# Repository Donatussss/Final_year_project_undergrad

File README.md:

# Water and Gas monitoring for automated oxygen and hydrogen production through electrolysis

### Project Aims
- Meet oxygen demand in hospitals
- Realise an affordable device to generate oxygen

This is our final year undergrad project
## Project designations
- Elec team
  - Monitor water levels in electrolysis chambers - Mitch
  - Monitor gas pressure, flowrate and concentration - Don

- Mech team
  - Dominic & Alphonso - develop electrolysis chamber

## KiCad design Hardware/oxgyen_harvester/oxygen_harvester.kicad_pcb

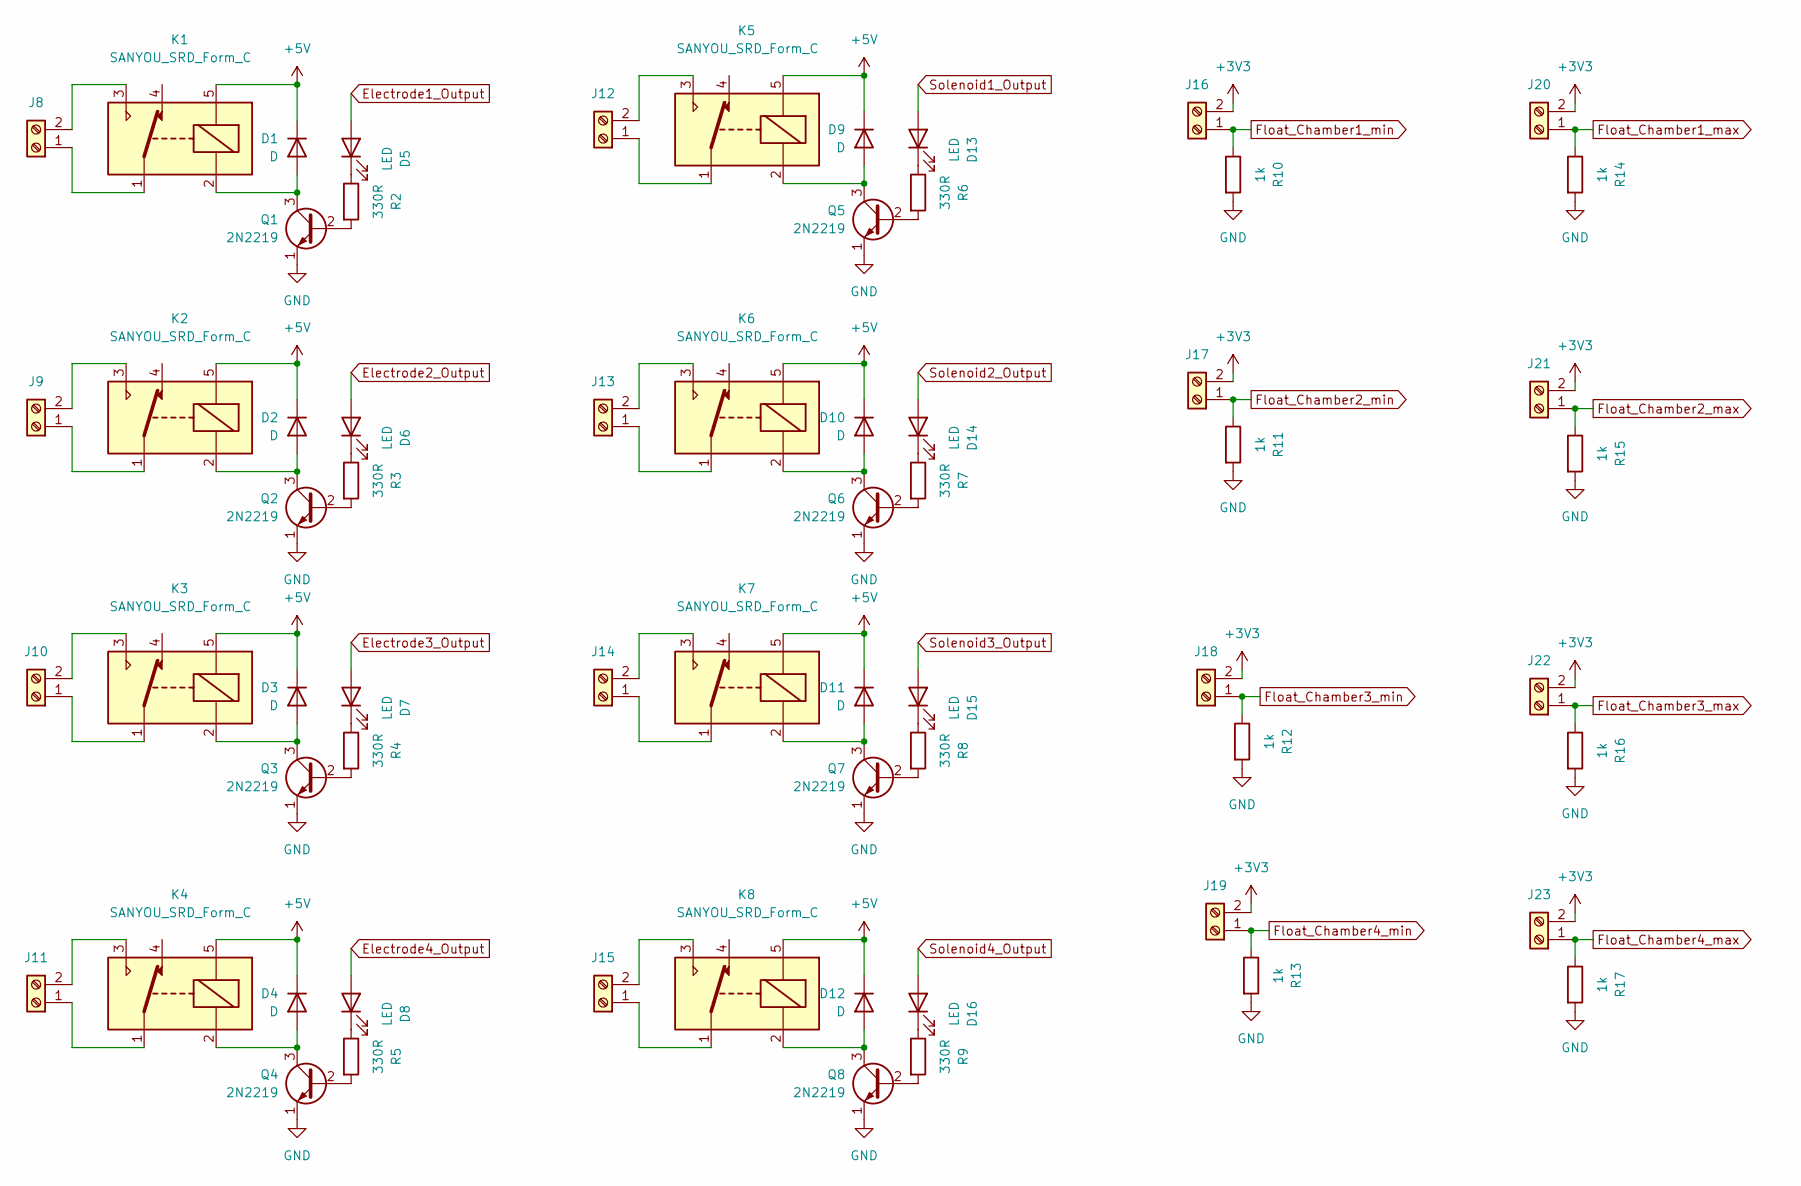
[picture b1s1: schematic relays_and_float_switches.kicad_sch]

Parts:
D1, D2, D3, D4, D9, D10, D11, D12: D; D_A-405_P10.16mm_Horizontal
D5, D6, D7, D8, D13, D14, D15, D16: LED; LED_D5.0mm_IRBlack
J8, J9, J10, J11, J12, J13, J14, J15, J16, J17, J18, J19, J20, J21, J22, J23: Screw_Terminal_01x02; TerminalBlock_bornier-2_P5.08mm
K1, K2, K3, K4, K5, K6, K7, K8: SANYOU_SRD_Form_C; Relay_SPDT_SANYOU_SRD_Series_Form_C
Q1, Q2, Q3, Q4, Q5, Q6, Q7, Q8: 2N2219; TO-92L_Inline
R2, R3, R4, R5, R6, R7, R8, R9: 330R; R_Axial_DIN0207_L6.3mm_D2.5mm_P10.16mm_Horizontal
R10, R11, R12, R13, R14, R15, R16, R17: 1k; R_Axial_DIN0207_L6.3mm_D2.5mm_P10.16mm_Horizontal

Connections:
+3V3: J16.2, J17.2, J18.2, J19.2, J20.2, J21.2, J22.2, J23.2; also elsewhere on the board
+5V: D1.1 (K), D2.1 (K), D3.1 (K), D4.1 (K), D9.1 (K), D10.1 (K), D11.1 (K), D12.1 (K), K1.5, K2.5, K3.5, K4.5, K5.5, K6.5, K7.5, K8.5; also elsewhere on the board
Electrode1_Output: D5.2 (A); also elsewhere on the board
Electrode2_Output: D6.2 (A); also elsewhere on the board
Electrode3_Output: D7.2 (A); also elsewhere on the board
Electrode4_Output: D8.2 (A); also elsewhere on the board
Float_Chamber1_max: J20.1, R14.1; also elsewhere on the board
Float_Chamber1_min: J16.1, R10.1; also elsewhere on the board
Float_Chamber2_max: J21.1, R15.1; also elsewhere on the board
Float_Chamber2_min: J17.1, R11.1; also elsewhere on the board
Float_Chamber3_max: J22.1, R16.1; also elsewhere on the board
Float_Chamber3_min: J18.1, R12.1; also elsewhere on the board
Float_Chamber4_max: J23.1, R17.1; also elsewhere on the board
Float_Chamber4_min: J19.1, R13.1; also elsewhere on the board
GND: Q1.1 (E), Q2.1 (E), Q3.1 (E), Q4.1 (E), Q5.1 (E), Q6.1 (E), Q7.1 (E), Q8.1 (E), R10.2, R11.2, R12.2, R13.2, R14.2, R15.2, R16.2, R17.2; also elsewhere on the board
unnamed: D1.2 (A), K1.2, Q1.3 (C)
unnamed: D2.2 (A), K2.2, Q2.3 (C)
unnamed: D3.2 (A), K3.2, Q3.3 (C)
unnamed: D4.2 (A), K4.2, Q4.3 (C)
unnamed: D5.1 (K), R2.1
unnamed: D6.1 (K), R3.1
unnamed: D7.1 (K), R4.1
unnamed: D8.1 (K), R5.1
unnamed: D9.2 (A), K5.2, Q5.3 (C)
unnamed: D10.2 (A), K6.2, Q6.3 (C)
unnamed: D11.2 (A), K7.2, Q7.3 (C)
unnamed: D12.2 (A), K8.2, Q8.3 (C)
unnamed: D13.1 (K), R6.1
unnamed: D14.1 (K), R7.1
unnamed: D15.1 (K), R8.1
unnamed: D16.1 (K), R9.1
unnamed: J8.1, K1.1
unnamed: J8.2, K1.3
unnamed: J9.1, K2.1
unnamed: J9.2, K2.3
unnamed: J10.1, K3.1
unnamed: J10.2, K3.3
unnamed: J11.1, K4.1
unnamed: J11.2, K4.3
unnamed: J12.1, K5.1
unnamed: J12.2, K5.3
unnamed: J13.1, K6.1
unnamed: J13.2, K6.3
unnamed: J14.1, K7.1
unnamed: J14.2, K7.3
unnamed: J15.1, K8.1
unnamed: J15.2, K8.3
unnamed: Q1.2 (B), R2.2
unnamed: Q2.2 (B), R3.2
unnamed: Q3.2 (B), R4.2
unnamed: Q4.2 (B), R5.2
unnamed: Q5.2 (B), R6.2
unnamed: Q6.2 (B), R7.2
unnamed: Q7.2 (B), R8.2
unnamed: Q8.2 (B), R9.2
Solenoid1_Output: D13.2 (A); also elsewhere on the board
Solenoid2_Output: D14.2 (A); also elsewhere on the board
Solenoid3_Output: D15.2 (A); also elsewhere on the board
Solenoid4_Output: D16.2 (A); also elsewhere on the board

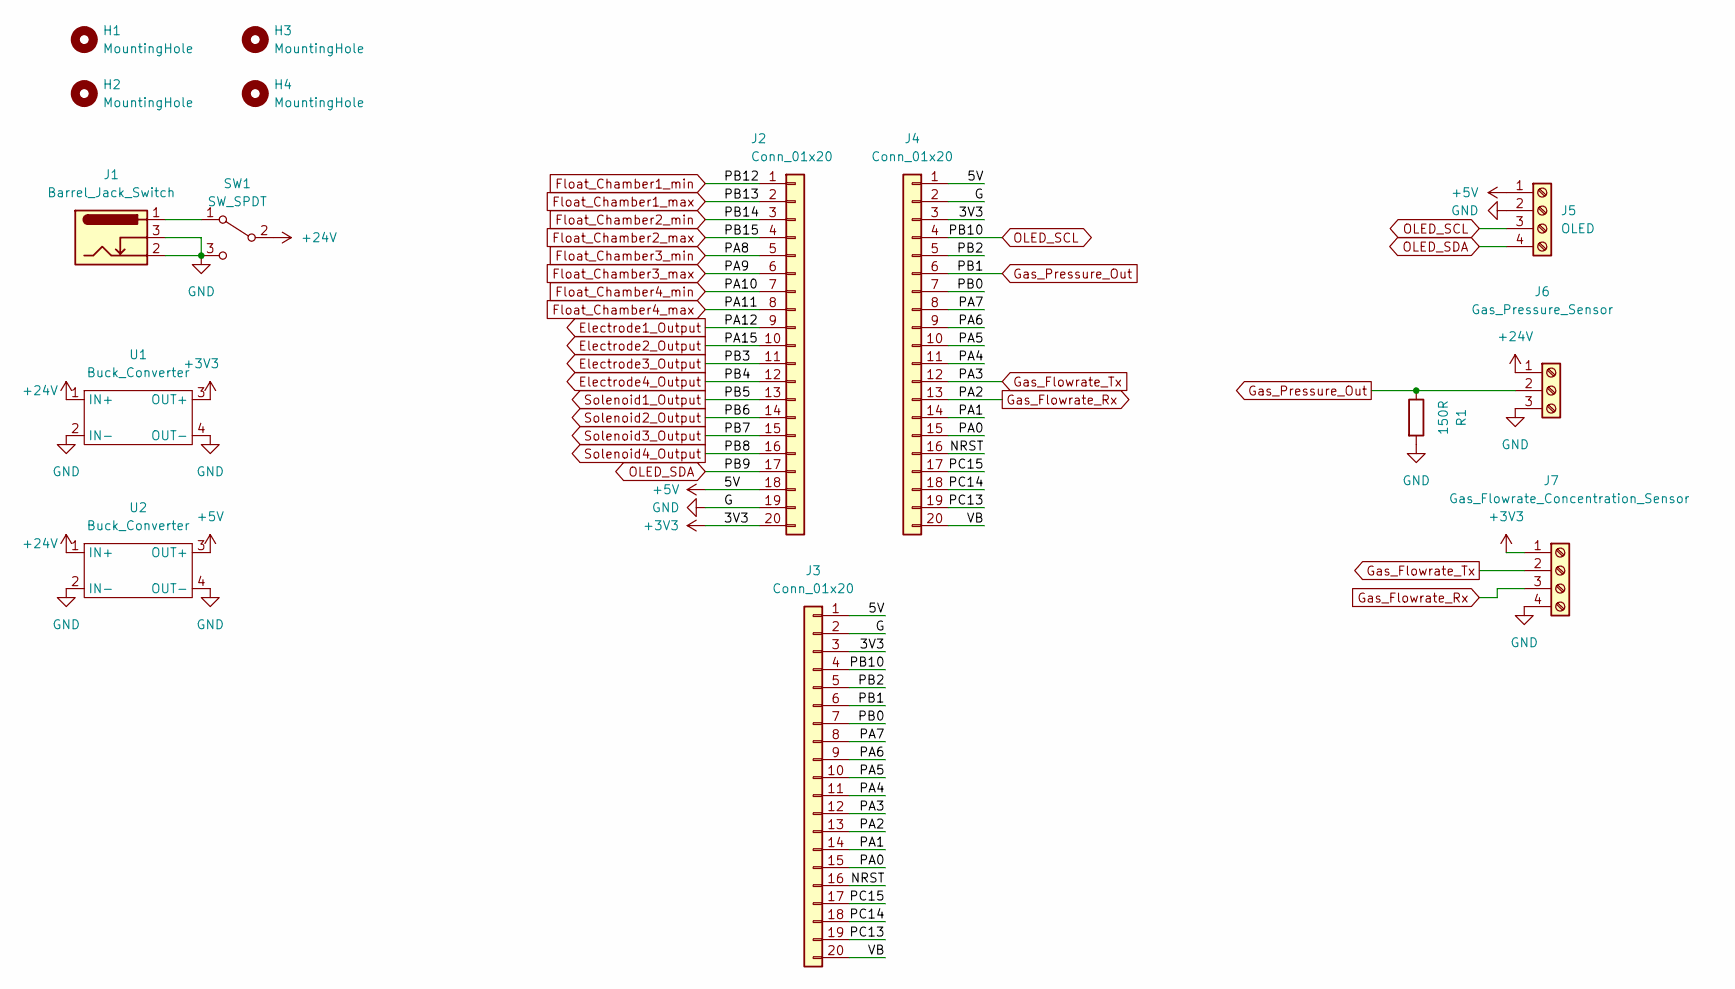
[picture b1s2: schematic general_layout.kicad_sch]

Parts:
H1, H2, H3, H4: MountingHole; MountingHole_4.3mm_M4_DIN965_Pad
J1: Barrel_Jack_Switch; BarrelJack_CUI_PJ-102AH_Horizontal
J2, J3, J4: Conn_01x20; PinSocket_1x20_P2.54mm_Vertical
J5: OLED; TerminalBlock_bornier-4_P5.08mm
J6: Gas_Pressure_Sensor; TerminalBlock_bornier-3_P5.08mm
J7: Gas_Flowrate_Concentration_Sensor; TerminalBlock_bornier-4_P5.08mm
R1: 150R; R_Axial_DIN0207_L6.3mm_D2.5mm_P10.16mm_Horizontal
SW1: SW_SPDT; PinSocket_1x03_P2.54mm_Vertical
U1, U2: Buck_Converter; Buck_converter

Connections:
+3V3: J2.20, J3.3, J4.3, J7.1, U1.3 (OUT+); also elsewhere on the board
+5V: J2.18, J3.1, J4.1, J5.1, U2.3 (OUT+); also elsewhere on the board
+24V: J6.1, SW1.2 (B), U1.1 (IN+), U2.1 (IN+)
/general_layout/NRST: J3.16, J4.16
/general_layout/PA0: J3.15, J4.15
/general_layout/PA1: J3.14, J4.14
/general_layout/PA4: J3.11, J4.11
/general_layout/PA5: J3.10, J4.10
/general_layout/PA6: J3.9, J4.9
/general_layout/PA7: J3.8, J4.8
/general_layout/PB0: J3.7, J4.7
/general_layout/PB2: J3.5, J4.5
/general_layout/PC13: J3.19, J4.19
/general_layout/PC14: J3.18, J4.18
/general_layout/PC15: J3.17, J4.17
/general_layout/VB: J3.20, J4.20
Electrode1_Output: J2.9; also elsewhere on the board
Electrode2_Output: J2.10; also elsewhere on the board
Electrode3_Output: J2.11; also elsewhere on the board
Electrode4_Output: J2.12; also elsewhere on the board
Float_Chamber1_max: J2.2; also elsewhere on the board
Float_Chamber1_min: J2.1; also elsewhere on the board
Float_Chamber2_max: J2.4; also elsewhere on the board
Float_Chamber2_min: J2.3; also elsewhere on the board
Float_Chamber3_max: J2.6; also elsewhere on the board
Float_Chamber3_min: J2.5; also elsewhere on the board
Float_Chamber4_max: J2.8; also elsewhere on the board
Float_Chamber4_min: J2.7; also elsewhere on the board
GND: J1.2, J1.3, J2.19, J3.2, J4.2, J5.2, J6.3, J7.4, R1.2, SW1.3 (C), U1.2 (IN-), U1.4 (OUT-), U2.2 (IN-), U2.4 (OUT-); also elsewhere on the board
Gas_Flowrate_Rx: J3.13, J4.13, J7.3
Gas_Flowrate_Tx: J3.12, J4.12, J7.2
Gas_Pressure_Out: J3.6, J4.6, J6.2, R1.1
unnamed: J1.1, SW1.1 (A)
OLED_SCL: J3.4, J4.4, J5.3
OLED_SDA: J2.17, J5.4
Solenoid1_Output: J2.13; also elsewhere on the board
Solenoid2_Output: J2.14; also elsewhere on the board
Solenoid3_Output: J2.15; also elsewhere on the board
Solenoid4_Output: J2.16; also elsewhere on the board

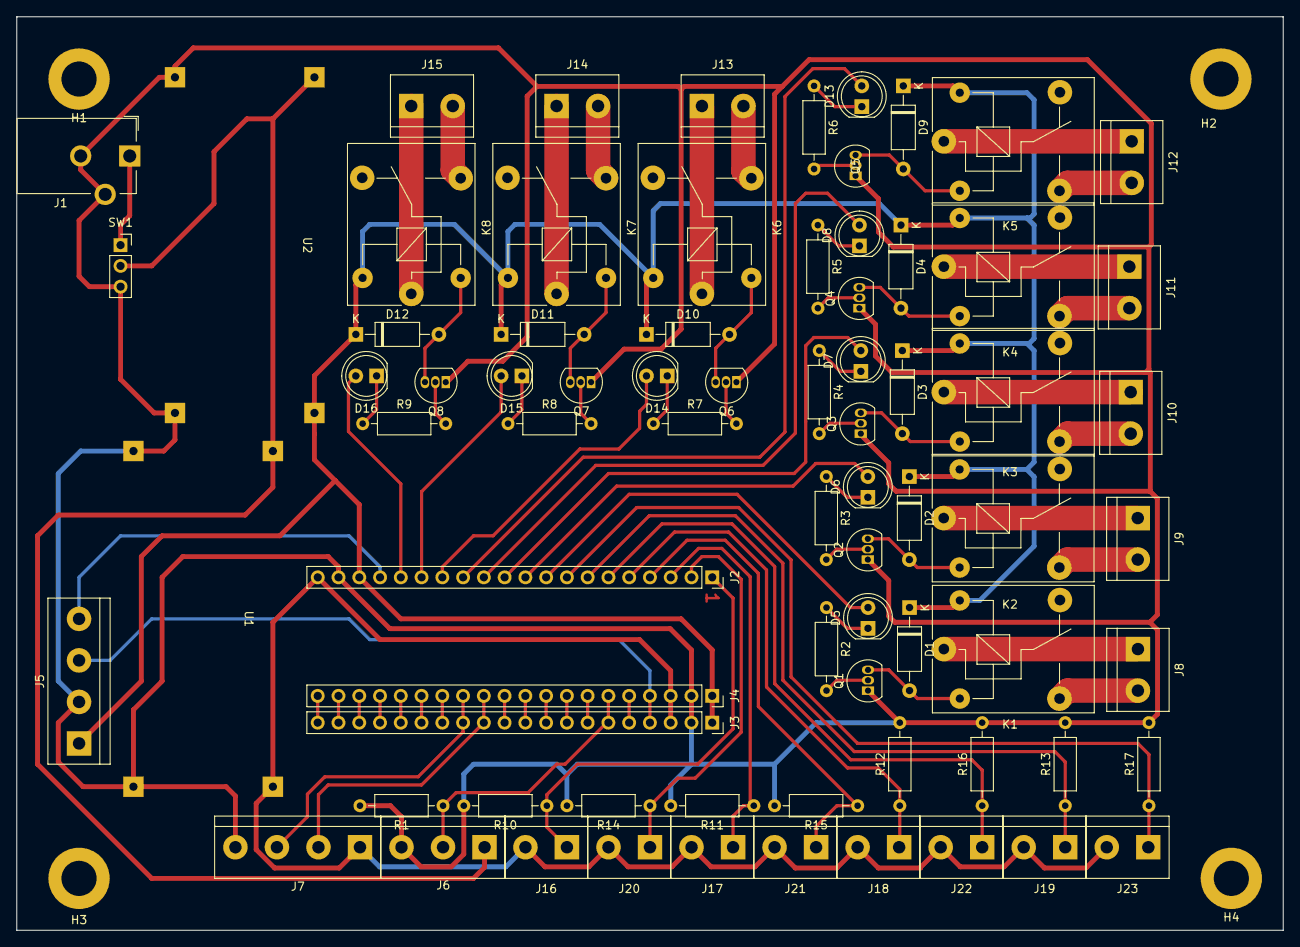
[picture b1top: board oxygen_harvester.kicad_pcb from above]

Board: 2 copper layers, 154.9 x 111.8 mm, 79 parts (0 on the bottom side), 79 nets.

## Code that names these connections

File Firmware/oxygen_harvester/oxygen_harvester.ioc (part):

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Mcu.Name=STM32F411C(C-E)Ux
Mcu.Package=UFQFPN48
Mcu.UserName=STM32F411CEUx
PA10.GPIOParameters=GPIO_Label
PA10.GPIO_Label=Float_Chamber4_min
PA10.Signal=GPIO_Input
PA11.GPIOParameters=GPIO_Label
PA11.GPIO_Label=Float_Chamber4_max
PA11.Signal=GPIO_Input
PA12.GPIOParameters=GPIO_Label
PA12.GPIO_Label=Electrode1_Output
PA12.Signal=GPIO_Output
PA13.Mode=Serial_Wire
PA13.Signal=SYS_JTMS-SWDIO
PA14.Mode=Serial_Wire
PA14.Signal=SYS_JTCK-SWCLK
PA15.GPIOParameters=GPIO_Label
PA15.GPIO_Label=Electrode2_Output
PA15.Signal=GPIO_Output
PA2.Mode=Asynchronous
PA2.Signal=USART2_TX
PA3.Mode=Asynchronous
PA3.Signal=USART2_RX
PA4.Mode=NSS_Signal_Hard_Input
PA4.Signal=SPI1_NSS
PA5.Mode=Full_Duplex_Slave
PA5.Signal=SPI1_SCK
PA6.Mode=Full_Duplex_Slave
PA6.Signal=SPI1_MISO
PA7.Mode=Full_Duplex_Slave
PA7.Signal=SPI1_MOSI
PA8.GPIOParameters=GPIO_Label
PA8.GPIO_Label=Float_Chamber3_min
PA8.Signal=GPIO_Input
PA9.GPIOParameters=GPIO_Label
PA9.GPIO_Label=Float_Chamber3_max
PA9.Signal=GPIO_Input
PB1.GPIOParameters=GPIO_Label
PB1.GPIO_Label=Gas_Pressure
PB1.Signal=ADCx_IN9
PB10.Mode=I2C
PB10.Signal=I2C2_SCL
PB12.GPIOParameters=GPIO_Label
PB12.GPIO_Label=Float_Chamber1_min
PB12.Signal=GPIO_Input
PB13.GPIOParameters=GPIO_Label
PB13.GPIO_Label=Float_Chamber1_max
PB13.Signal=GPIO_Input
PB14.GPIOParameters=GPIO_Label
PB14.GPIO_Label=Float_Chamber2_min
PB14.Signal=GPIO_Input
PB15.GPIOParameters=GPIO_Label
PB15.GPIO_Label=Float_Chamber2_max
PB15.Signal=GPIO_Input
PB3.GPIOParameters=GPIO_Label
PB3.GPIO_Label=Electrode3_Output
PB3.Signal=GPIO_Output
PB4.GPIOParameters=GPIO_Label
PB4.GPIO_Label=Electrode4_Output
PB4.Signal=GPIO_Output
PB5.GPIOParameters=GPIO_Label
PB5.GPIO_Label=Solenoid1_Output
PB5.Signal=GPIO_Output
PB6.GPIOParameters=GPIO_Label
PB6.GPIO_Label=Solenoid2_Output
PB6.Signal=GPIO_Output
PB7.GPIOParameters=GPIO_Label
PB7.GPIO_Label=Solenoid3_Output
PB7.Signal=GPIO_Output
PB8.GPIOParameters=GPIO_Label
PB8.GPIO_Label=Solenoid4_Output
PB8.Signal=GPIO_Output
PB9.Mode=I2C
PB9.Signal=I2C2_SDA
PH0\ -\ OSC_IN.Mode=HSE-External-Oscillator
PH0\ -\ OSC_IN.Signal=RCC_OSC_IN
PH1\ -\ OSC_OUT.Mode=HSE-External-Oscillator
PH1\ -\ OSC_OUT.Signal=RCC_OSC_OUT
RCC.HSE_VALUE=25000000
RCC.SYSCLKFreq_VALUE=96000000
RCC.SYSCLKSource=RCC_SYSCLKSOURCE_PLLCLK
board=custom

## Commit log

2024-03-23 Proper first commit
2024-04-10 water control
2024-04-19 Hardware and software changes
2024-04-19 Added oled display code and gas control update
2024-05-01 Removed chamber 3 control
2024-05-01 adding water maintenance
2024-05-01 Updated cubeide
2024-05-02 Added release build
2024-05-03 Added initialization display and removed chamber management
2024-05-04 Added water control modifications and display updates
2024-05-20 Latest changes in firmware hardware and documentation
2024-07-13 Added final changes and documentation
